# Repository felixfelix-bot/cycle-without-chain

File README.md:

# cycle-without-chain

An **independent-cadence, chainless electric drivetrain for a bicycle**: the rider
pedals a generator, a power-electronic bus moves the energy, and hub motors drive
the wheels. Cadence is decoupled from road speed, so the rider can pedal at a
comfortable speed and torque while the electronics do the job a gear train would
otherwise do.

> **STATUS: DESIGN PHASE. NOT SAFE TO ENERGIZE. NOT FABRICATED. NOT ROAD LEGAL.**
> A schematic and a body of analysis exist. There is no PCB, no assembly, no
> energised hardware and no measured prototype performance. Nothing here
> authorises building, powering or riding anything. The safety architecture below
> is an intent backed by calculations, not a qualified design.

## What is being built

**pedals → generator → controlled DC bus → hub motor(s) → wheels.** There is no
chain to the rear wheel.

- **Two motor/generator bridges** driven by DRV8353 smart gate drivers, six 2 mΩ
  low-side shunts, a 29-MOSFET population. Generator and motor are electrically
  independent, which is what makes cadence independent of road speed.
- **Rider effort is a generator load**, not a mechanical coupling. Pedal
  resistance is set electrically; arbitrary cadence and arbitrary power cannot
  both be enforced simultaneously, and the rider/generator balance has to be
  managed.
- **Mechanical friction brakes remain mandatory and are not replaced** by
  electrical braking. Regeneration is only commanded by actual rider brake
  intent — never by a map, a predicted hill or a control loop.
- **Fault shutdown is separate from normal braking**, and must work whether or not
  the microcontroller has booted.

## Storage: LTO pack plus supercapacitor buffer

Chemistry is fixed by the operator: **lithium titanate (LTO) for usable energy, a
supercapacitor bank for power.** The split follows the duty this vehicle actually
has — a short-duration buffer for starts, stops and brief deficits, with no
powered-range target.

- Preferred string to evaluate: **20s Toshiba SCiB 2.9 Ah cells** — 56.0 V max,
  48.0 V nominal, 36.0 V min, ≈139 Wh and ≈3.0 kg cells only.
- **56.0 V sits inside the existing 36–58.4 V bus envelope**, so the bus voltage
  survives the LTO decision. This is a window fit, not a compatibility proof:
  loaded terminal voltage under pulse current, tolerance stack-up, fuse and
  disconnect behaviour, and cold/full charge acceptance all remain open.
- The supercapacitor branch (candidate: Eaton XV3550 20s, ≈1.24 kg, ≈3.9 Wh usable)
  is **not additive by default**. It is justified only if measured braking energy
  demonstrably exceeds LTO charge acceptance, or if cold operation requires it.

Record: [storage decision](docs/design/storage-decision-lto.md).

## What the trade study found

Why this project needs a careful design phase rather than a fast build:

- A waxed derailleur chain is roughly **96%** efficient. A series electrical path
  is not, and every conversion stage compounds.
- A realistic purpose-built PM generator path — generator × rectifier × controller
  × motor ≈ 93% × 97% × 98% × 90% — lands near **80%**, roughly a **20-point
  loss**. An automotive claw-pole alternator at bicycle cadence is far worse
  (≈21–39%) because those machines are built for 1500+ rpm.
- Consequence: at equal wheel output the rider must produce roughly **20% more
  pedal power** than with a chain. That is the price of independent cadence and
  the single number to decide against.
- Cases where a series drivetrain genuinely earns its losses: long-wheelbase cargo
  bikes, velomobiles with many idlers, and layouts where crank speed must be
  decoupled from wheel speed. A simple bicycle with a chain does not need this.

The study, its assumptions and its known accounting errors:
[docs/analysis/chainless-drivetrain.md](docs/analysis/chainless-drivetrain.md). Its
model is retained **unchanged** for audit, including the errors.

**Published correction:** earlier notes claimed Mando Footloose and Schaeffler Free
Drive use automotive claw-pole alternators and deliver ~32% pedals-to-road. No
verified generator-efficiency map exists for either product. Do not reuse that
figure as a product specification. See
[the illustrated guide](docs/analysis/parallel-hybrid-guide.md) for source boundaries.

## Schematics

`hardware/powerboard-reva/` is a Python generator that emits a hierarchical
**KiCad 9** schematic, native netlist, PDF and SVG. Current state:

- **387 components, 220 nets, 1142 connected pins, 51 explicit NCs, 32 pages.**
  The pre-change baseline was re-measured from a fresh clone at `ae42054`
  (382 components, 218 nets, 1129 pins): [schematic figure verification](docs/design/schematic-figures-verified.md).
  The current figures include the DRIVE12 OVP comparator, its divider and the L501 change.
- **49 hardware tests** pass, normally and under `python3 -O`.
- Strict ERC: **0 errors, 0 warnings, exit 0** — the ten former undriven-supply
  findings are resolved by ten justified `PWR_FLAG`s (see
  `docs/design/erc-power-flags.md`); the verifier now requires ERC to be empty.
  Enumerated, gate-enforced and treated as open work, not silenced.
- Blocks present: dual DRV8353 bridges; protected-entry *intent* (fuse, shunt
  reverse clamp, 22 Ω resistor precharge, back-to-back TPSI3052-driven MOSFET
  pairs); fast overcurrent comparators; dual FSR brake frontends; rail partition
  (pack→CTRL3V3, bus→SINK12 always-on safety chain, delayed DRIVE12→MCU3V3) with
  an independent DRIVE12 output OVP comparator; and a pack-side control supply.
- **Inhibit resistors hold every switch off without firmware** — fitted 0 Ω ties,
  deliberately present, not to be removed.

**What does not exist:** no `.kicad_pcb`, no placement, no routing, no Gerbers, no
priced purchase BOM, no assembled board, no bench measurement of any kind.

## The definition of done

[Open gates register](docs/design/open-gates-register.md) states what is proven and
what is not: **109 gates**, each classified by the kind of evidence that closes it.

- **A — closable now** by calculation, part selection, topology change or
  simulation, without hardware.
- **B — needs a built board** (thermal, ripple, effective capacitance under DC
  bias, start-up sequencing, EMI, hot-plug, pulse/SOA, main-switch conduction).
- **C — needs an operator decision.**
- **D — resolved**, with the commit that closed it.

Per-bucket counts are deliberately **not** repeated here. They move whenever a gate
is closed, and a stale copy in the README is exactly the drift this register exists
to prevent. The register's own summary table is authoritative, and
`analysis/gates/register_check.py` fails if it disagrees with the rows above it.

**The design phase is complete when every A gate is closed and every B and C gate
is explicitly deferred to a named phase with a named owner.** It is not complete
when the board works, because the board has never existed. Finishing the register
claims no electrical safety, no road legality and no manufacturing readiness.

That document is kept honest mechanically: `analysis/gates/register_check.py` fails
if a row has no bucket, no citation or a duplicate ID, or if the bucket counts
disagree with the summary table. It verifies the register is complete and
countable — not that any engineering claim inside it is true.

### Decisions still needed from the operator

Each is a C gate with its consequence recorded in the register:

1. **Architecture** — the study recommends the parallel hybrid; the chainless
   series version is an explicit overrule. Recording it matters because it sets the
   ~20-point rider-power cost and removes pedalling home on a flat battery.
2. **Road class and jurisdiction** — sets lawful power, speed and control topology.
3. **Motor and generator** — pole count, Kv, winding. Bus voltage, shunts, trip
   points, regen ceiling and body-diode energy all follow from it.
4. **Pack and BMS** — exact cell, series count, current limits, source impedance.
5. **Mass and frame** — weighed bicycle mass, frame and fork, permitted mounting.
6. **Duty and route** — descent grades, duration and ambient, which set the braking
   sink rating.
7. **Test authority** — what energy may be tested, in what guarded setup, signed
   off by whom. Every B gate is blocked until this exists.
8. **Independent reviewer** — no review in this corpus can claim cross-family
   independence.

## Quality gates

The board tooling was rebuilt after auditing a previous project where a failed DRC
subprocess reported zero violations — a fail-open check that reads as a clean board.
Those lessons are executable here, not documented intent:

- `tools/gates/native_reports.py` — KiCad export/DRC/ERC runner. A nonzero exit, a
  missing or unparsable report, a stale report, or a zero-object scan is
  **FAILURE**, never success.
- `tools/gates/netlist_parity.py` — exact `(reference, pin, net)` set comparison.
  Counts are never compared, because a gate/source swap keeps the count identical.
- `tools/gates/release_manifest.py` — manufacturing artifact inventory rejecting
  placeholder, truncated or missing outputs, including a requested inner layer that
  produced no file.
- `tools/gates/run_all_gates.py` — one nonzero status if any gate fails; a crashed
  or unwired gate reports **NOT RUN**, never green.

**237 gate tests pass**, normally and under `python3 -O`, with negative controls
proving each gate can actually fail.

## Use cases under investigation

These are **hypotheses to test, not market validation**. The series concept trades
conversion losses, added mass and control complexity for cadence independent of
road speed, controllable pedal resistance and chassis freedom. This is research,
not a certified product.

- **Cargo and urban logistics:** a comfortable cadence through stops and changing
  road speeds. Payload and hill capability remain bounded by motor torque,
  available power, storage state and thermal limits — not guaranteed.
- **Adaptive cycling and rehabilitation research:** adjustable pedal resistance
  could support experiments with different rider abilities. Suitability requires
  individual assessment; no medical safety or treatment claims.
- **Low-maintenance, clean commuters:** removing the wheel-drive chain could reduce
  chain grime and servicing, but does not guarantee lower total maintenance. The
  crank-to-generator gearing remains moving machinery and needs a guard.
- **Recumbent, velomobile and alternative-chassis designers:** electrical routing
  could replace long wheel-drive chains and free up layout, subject to generator
  packaging, structural loads, mass and heat rejection.
- **Stationary exercise and pedal charging:** controlled resistance could convert
  rider effort into stored energy — not free energy. Requires a safe, stable stand
  and wheel-propulsion inhibit. At full storage, useful charging stops; continued
  pedalling under load needs a safe energy sink and cooling.

### Balance assistance — research option, not a feature

An actively gimballed flywheel might assist stopping, starting and mounting for
riders with balance limitations. This is an accessibility hypothesis, not
demonstrated safety or fall prevention, and it is compared against mechanically
supported cycles including tricycles.

Energy scales with rotor speed squared; angular momentum only linearly. Discharging
the rotor reduces balancing authority. Two gimbal axes do not eliminate torque
coupling, travel limits, singularities or power-failure risk. The suggested 8–12 kg
mass and 30% range penalty are unverified examples, not specifications. Never claim
recovery from ice, potholes, collisions or arbitrary disturbances, and never claim
the rider cannot tip over. High-speed rotor safety needs specialist mechanical
engineering, not electrical PCB checks.

[Quantified feasibility study](docs/design/gyro-balance-feasibility.md) — calculations
and a source-backed shortlist, not a purchase BOM. No gyro hardware is selected, and
mechanical brakes and support are not replaced.

## Repository map

- `hardware/powerboard-reva/` — schematic generator, tests, committed netlist/PDF/SVG
  exports. The generator is the source of truth, not the exports.
- `docs/design/` — per-block milestone and review documents, the
  [open gates register](docs/design/open-gates-register.md), the
  [LTO storage decision](docs/design/storage-decision-lto.md), and the gyro study.
- `docs/analysis/` — drivetrain trade study, historical model, diagrams.
- `analysis/` — executable models with tests: precharge, braking, storage, gyro,
  navigation, FSR, register consistency.
- `tools/gates/` — the fail-closed release gates.
- `docs/evaluation/`, `docs/research/`, `docs/PLAN-parallel-hybrid.md` — **historical**
  concept and sourcing research from the parallel-hybrid baseline. Not validated
  purchasing evidence, and not the current implementation plan.

## Reproduce

```sh
# drivetrain trade study (stdlib only)
python3 docs/analysis/chainless_drivetrain_model.py

# schematic, netlist, PDF and SVG
cd hardware/powerboard-reva && python3 generate_schematic.py

# hardware test suite, both modes
cd hardware/powerboard-reva && python3 -m unittest discover -s tests
cd hardware/powerboard-reva && python3 -O -m unittest discover -s tests

# fail-closed release gates — pytest only, see the note below
python3 -m pytest tests/gates -q

# open-gates register consistency
python3 analysis/gates/register_check.py docs/design/open-gates-register.md
```

### `tests/gates` has no unittest route

Every test under `tests/gates` is a **bare module-level function**, and the whole
directory contains **zero `unittest.TestCase` classes**. `python3 -m unittest
discover -s tests/gates` exits **0** reporting `Ran 0 tests … OK`: it grades
nothing. Adding `tests/gates/__init__.py` does not change this — the collection
unit unittest looks for is a `TestCase` subclass, which these files do not have.

That is why the gate count is quoted from `python3 -m pytest tests/gates -q`
(**237**) and never from a unittest command. If you add a gate test, use pytest
and keep it a function; converting the directory to `TestCase` classes would be a
deliberate change to how the suite is collected, not a cleanup.

The hardware suite under `hardware/powerboard-reva/tests` is different: it is
`unittest` throughout, so the `unittest discover` command above is correct there
and reports **49** tests.

Passing tests prove the models and the generated connectivity behave as specified.
They do not prove the circuit is electrically safe, fabricable or rideable.

## Remotes

The repository is published in two places, and both are live:

- **GitHub** — `origin`, <https://github.com/felixfelix-bot/cycle-without-chain>
- **nostr (NIP-34)** — `ngit`, via `relay.ngit.dev`

```
git clone nostr://npub1tc6a0gdsu5l5gplyxflgwy9aq29jyelj9rv65syyukx3setl0usq9npkea/relay.ngit.dev/cycle-without-chain
```

Web view: <https://gitworkshop.dev/npub1tc6a0gdsu5l5gplyxflgwy9aq29jyelj9rv65syyukx3setl0usq9npkea/relay.ngit.dev/cycle-without-chain>

Push to both with `git push origin master && git push ngit master`. The nostr
identity (`npub1tc6a0…`) is dedicated to this repository; its secret is held in
ngit's local file store, not in this tree.

*Earlier history: the repository previously carried a ngit remote for
`npub1nng5…` that never had a published announcement, so it was a dangling
coordinate rather than a working mirror. It was replaced by the current identity
on 2026-11-11; the old coordinate is dead and should not be used.*

## License

Model and analysis code MIT; documentation separately licensed. See `LICENSE`.

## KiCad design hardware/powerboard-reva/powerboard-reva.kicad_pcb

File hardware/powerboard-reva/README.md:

# Powerboard Rev A — populated, partial schematic milestone

**NOT SAFE TO ENERGIZE. NOT FABRICATION-READY. No PCB, routing, procurement or riding authorization.**

Open `powerboard-reva.kicad_pro` or root `powerboard-reva.kicad_sch` in KiCad 9. The root references twenty-six real child sheets. Nets join electrically through explicitly named global labels; GEN_ and HUB_ prefixes separate bridge/control signals. This is not a block-diagram-only drawing or connector substitution for ICs.

## Selected FSR circuit milestone (current; supersedes historical counts below)

Two actual OPA333AIDBVR + TMUX1511PWR channels now replace the rider Hall inputs.
See [FSR implementation](docs/fsr-implementation.md). The binary switch topology remains;
its authority is a **firmware contract, not a hardware positive-torque guard**.
27 pages, 314 components, 181 connected nets, 956 connected endpoints, 51 explicit NCs.
Strict ERC returns **5**, with **5 unresolved errors / 0 warnings**; no suppression.
Candidate TVS/clamps are not battery-short protection. Low-voltage frontend bench use
only after independent review; this does not authorize energizing the powerboard.

## Current MCU milestone (historical; superseded by FSR counts above)

See [MCU integration review](../../docs/design/mcu-integration-review.md) for reproduced checks, pending cross-family approval and prioritized next circuit blockers. [MCU milestone](../../docs/design/mcu-milestone.md): real STM32G474VET6 circuit, 15 pages, 199 components, 642 connected endpoints and 45 explicit NC pins. Native ERC: four unresolved errors, zero warnings. Firmware, fast overcurrent trip, protected entry, storage acceptance and sequencing remain blockers. Historical sections below are not current status.

## Current protection integration — UNSAFE DRAFT

The sections below record the **earlier six-page milestone**, not current counts.
Current integration has 10 pages, 130 components, 104 nets and 452 endpoints;
VM now uses bus-fed AUX12V. Four added protection sheets remain unqualified.
See [independent integration review](../../docs/design/protection-integration-review.md)
for current evidence and prioritized blockers. ERC still has three errors
(U1.24 VREF, U1.25 AGND, U3.1 DC_LINK). No release approval.

## Implemented (historical six-page milestone)

- Two **DRV8353SRTAT** SPI drivers, 40 signal pins plus exposed pad, from TI SLVSDY6A pp6–7.
- Twelve **CSD19532Q5B** MOSFETs using embedded, inheritance-resolved stock KiCad symbols; three half-bridges per machine.
- Twelve provisional 4R7 gate resistors and twelve 100k gate-source pull-downs.
- Six 2mOhm low-side shunts, each wired to the corresponding SPx input and low-side sources; SNx to PGND. Kelvin layout is mandatory and not yet implemented.
- Driver charge-pump, regulator and supply capacitors; ENABLE pull-downs; SPI SDO/nSCS and fault pull-ups.
- Six provisional local 1uF/100V bus ceramics and one provisional 100uF/100V bulk capacitor.
- Eleven explicitly external connectors for machine phases, protected DC input, regulated supplies, independent enable chain, MCU PWM/SPI/ADC.

VM deliberately uses externally regulated 12V; VDRAIN senses the shared bus. VREF is 3.3V, **not** 1.65V: CSA midpoint comes from internal VREF/2. Gain20 and driver protection configuration require software plus hardware review; no configuration is implied by the drawing.

## Executed verification (KiCad CLI 9.0.9)

Run `python3 export_artifacts.py` from this directory. Python standard library and installed KiCad symbol libraries are sufficient; no SKiDL runtime required. Direct native schematic generation was used to deliver loadable drawings, not only a netlist.

- Six loadable hierarchical pages: root, GEN driver, GEN bridge, HUB driver, HUB bridge, external boundaries.
- **84 components, 80 exported nets, 308 pin assignments** checked against the actual KiCad-exported netlist by `verify_exports.py`.
- Actual six-page PDF: `exports/powerboard-reva.pdf`.
- Six nonempty SVG pages: `exports/svg/`.
- Actual netlist: `exports/powerboard-reva.net`.
- Actual ERC: `exports/erc.rpt` — **3 errors, 0 warnings**, all `power_pin_not_driven` for external AUX12V_EXT, LOGIC3V3_EXT and PGND supply boundary. No PWR_FLAG or waiver masks these unresolved boundaries. CLI exiting zero is not a clean ERC verdict.
- Machine-readable counts: `exports/verification.json`; component list `review-bom.csv`; exact mapping `pin-net-map.csv`.
- PDF bridge page visually inspected: real populated circuit visible, no clipping/major block overlaps, but dense local MOSFET labels need drawing cleanup before formal review.

## Explicit release blockers

This intentionally **does not implement** the complete eight-sheet concept. Missing: fused/reverse-protected/precharged power entry, DC contactor and discharge, independent OV comparator/chopper/resistor/thermal cutout, current comparator and latched fault chain, brake interlock, watchdog, UVLO, auxiliary buck/3V3 rails, bus-current INA240 circuit, MCU/SWD/timer/ADC mux, Hall/encoder/temperature interfaces and storage/BMS acceptance logic. No optional storage DC/DC exists.

External connectors are interface contracts for those unfinished circuits, **not evidence that they exist**. ENABLE pull-downs and integrated driver OCP are not a complete safety system. PM machines can charge the bus through body diodes even with all gates off. No validated thermal/ripple/transient model, source interrupt ratings, EMC review or full-energy test exists.

DRV footprint is deliberately blank pending exact RTA land-pattern/thermal-pad verification (pad41 is a schematic convention). Many passive and connector footprints are unselected. Stock MOSFET and shunt footprints are candidate mappings, not fabrication qualification. Gate resistances, capacitor values and connector pin orders are provisional, not an orderable BOM. No unselected safety part is disguised as a DNP implementation.

Independent review must validate electrical and physical pin maps against primary package drawings, supply sequencing/back-powering, CSA calibration/PWM sampling, gate drive/current/OCP settings and all safety failure modes. Then close ERC and protection design before any layout release. Reviewers should retain the honest partial status even though all connectivity assertions pass.

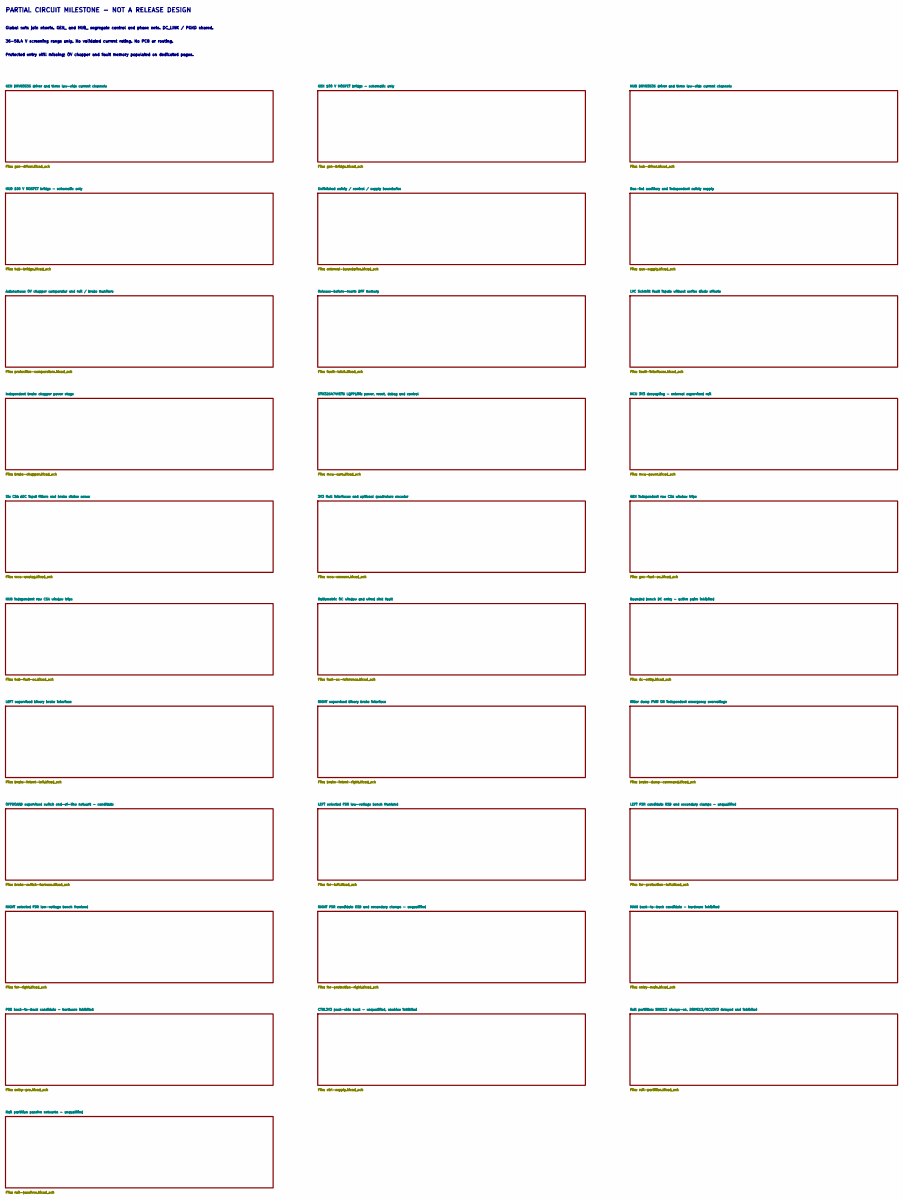
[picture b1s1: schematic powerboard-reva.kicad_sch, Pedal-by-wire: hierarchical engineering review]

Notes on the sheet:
PARTIAL CIRCUIT MILESTONE - NOT A RELEASE DESIGN
Global nets join sheets. GEN_ and HUB_ segregate control and phase nets. DC_LINK / PGND shared.
36-58.4 V screening range only. No validated current rating. No PCB or routing.
Protected entry still missing; OV chopper and fault memory populated on dedicated pages.

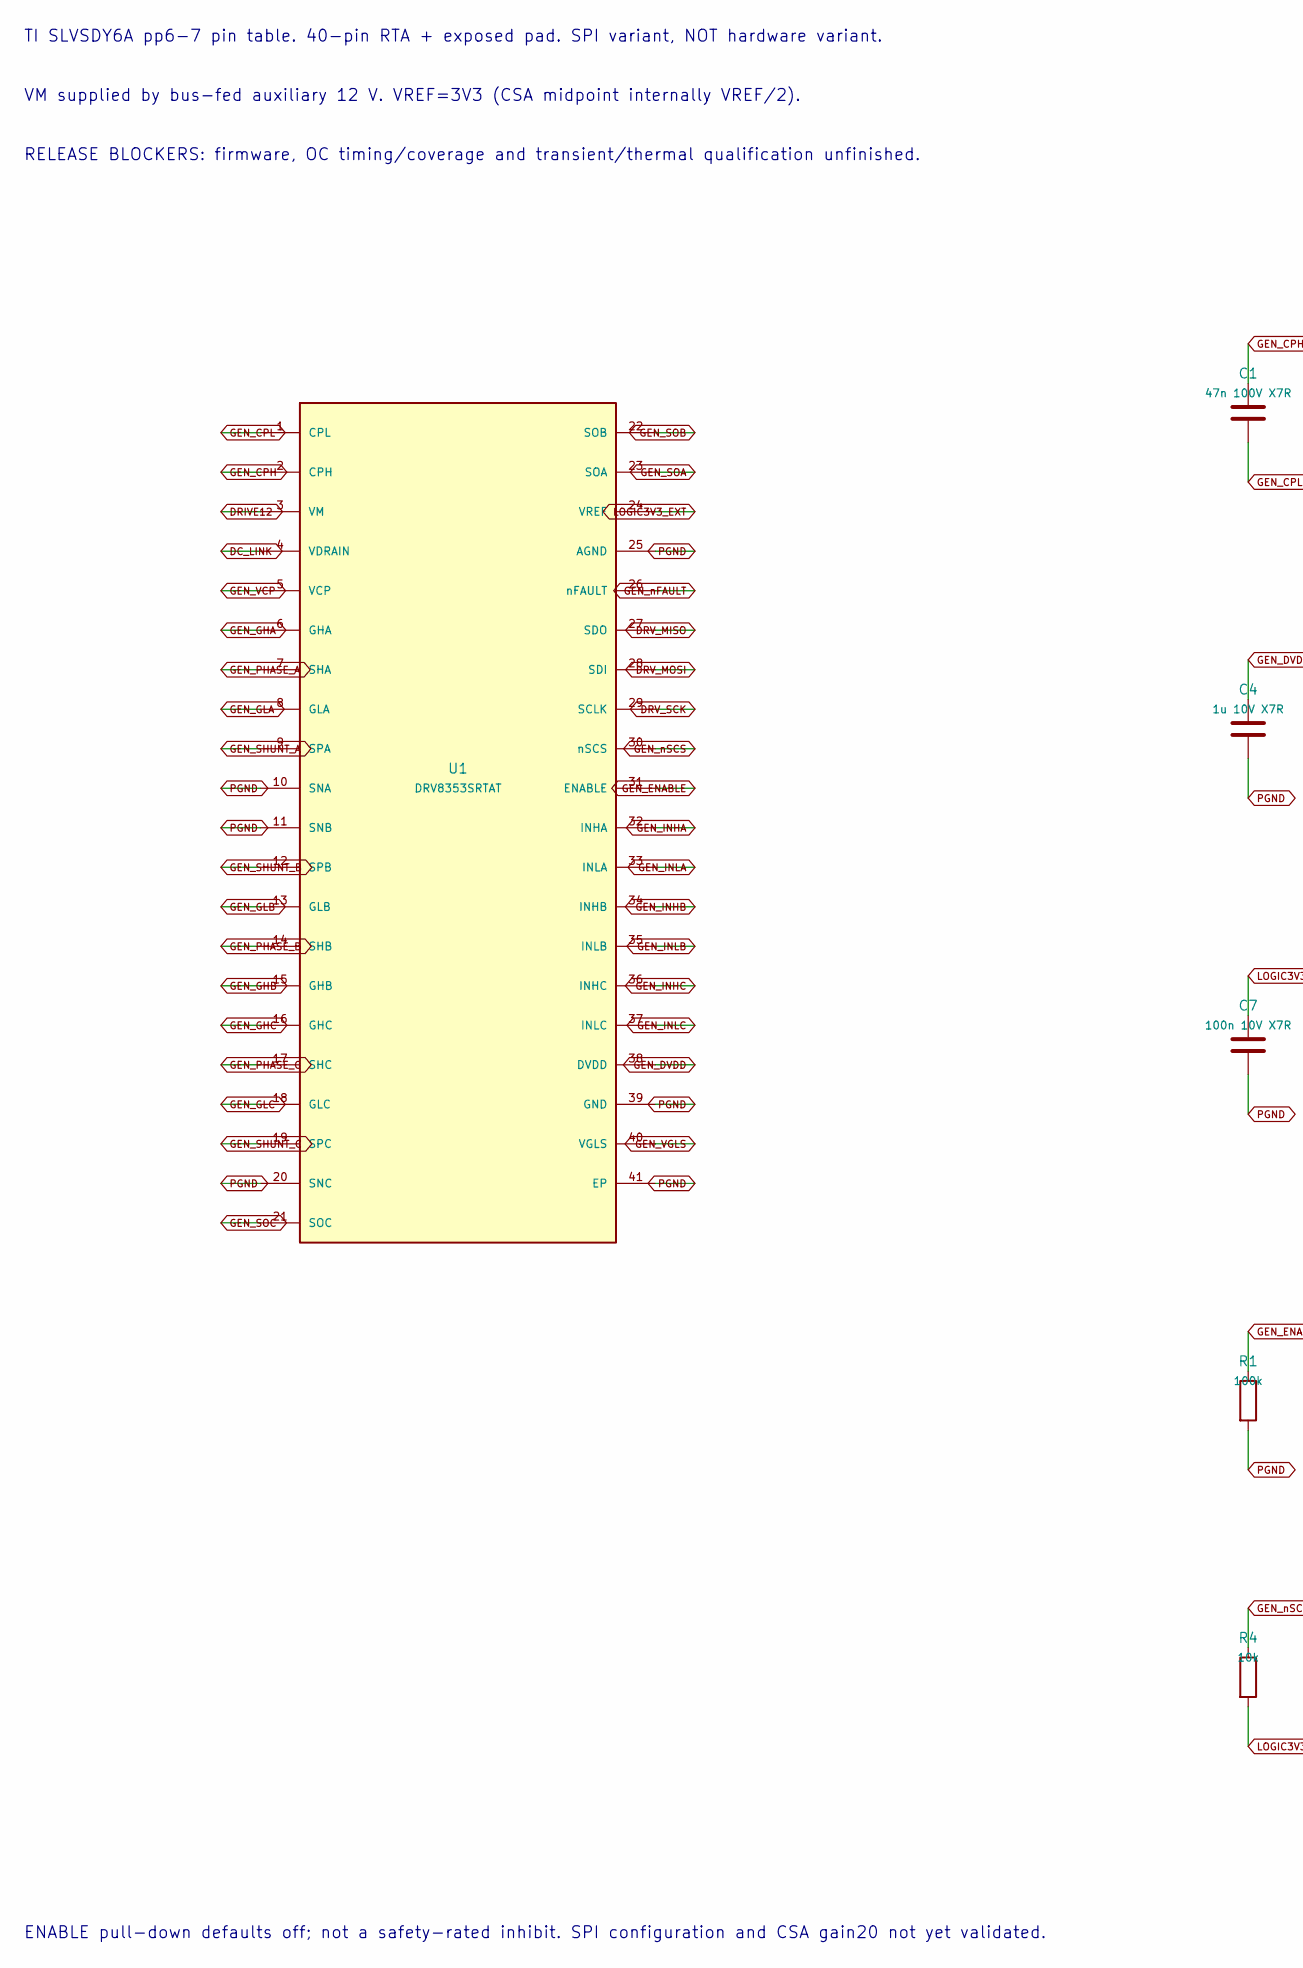
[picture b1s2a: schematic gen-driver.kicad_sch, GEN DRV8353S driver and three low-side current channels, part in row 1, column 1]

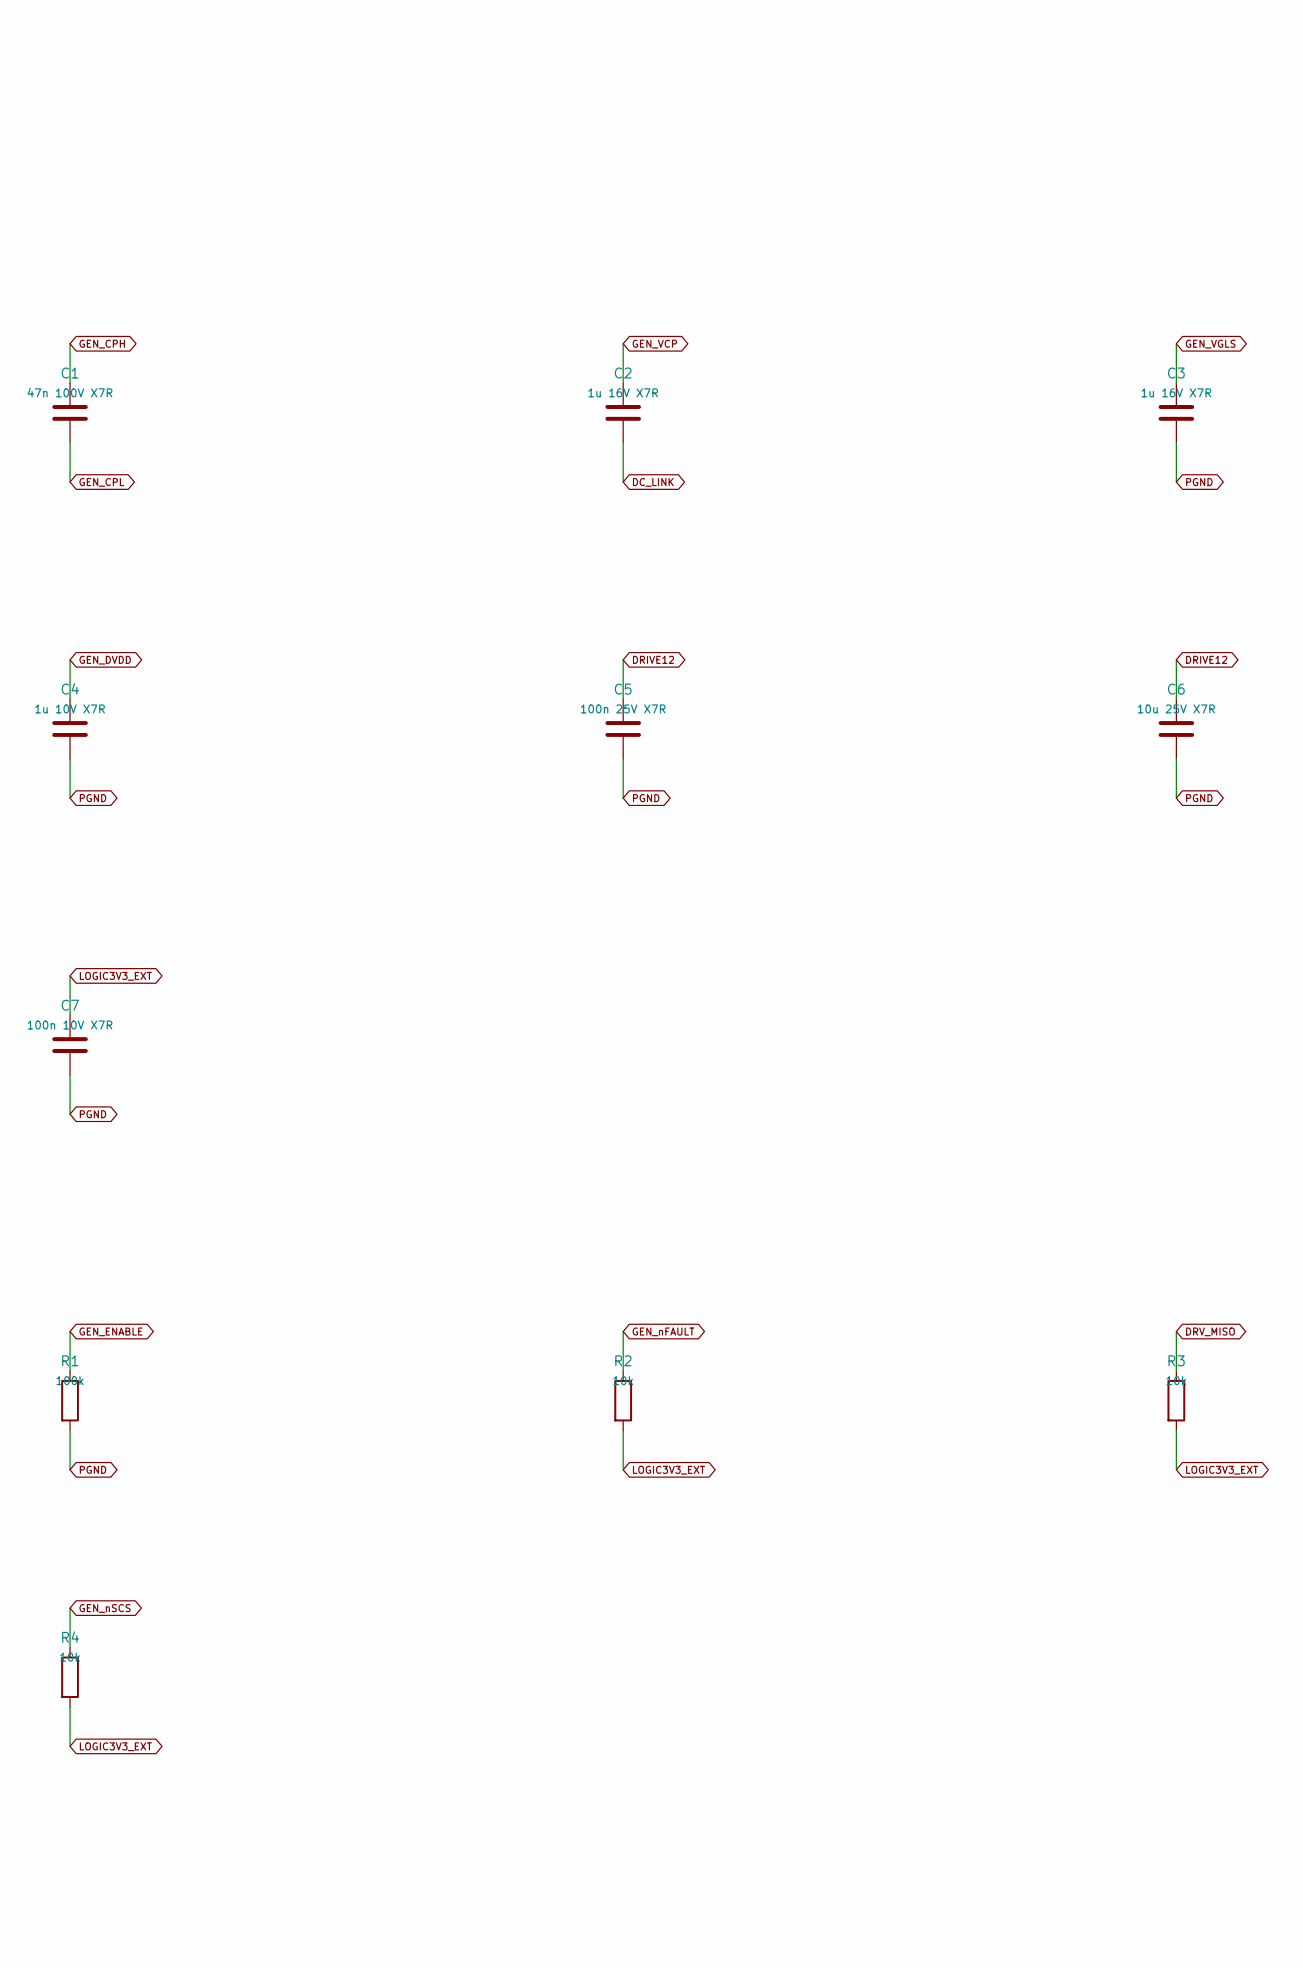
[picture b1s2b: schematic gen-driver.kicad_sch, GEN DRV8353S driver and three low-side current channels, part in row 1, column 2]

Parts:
C1: 47n 100V X7R; C_0805_2012Metric
C2, C3: 1u 16V X7R; C_0805_2012Metric
C4: 1u 10V X7R; C_0603_1608Metric
C5: 100n 25V X7R; C_0805_2012Metric
C6: 10u 25V X7R; C_0805_2012Metric
C7: 100n 10V X7R; C_0603_1608Metric
R1: 100k; R_0805_2012Metric
R2, R3, R4: 10k; R_0805_2012Metric
U1: DRV8353SRTAT; QFN-40-1EP_6x6mm_P0.5mm_EP4.6x4.6mm

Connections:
DC_LINK: C2.2, U1.4 (VDRAIN); also elsewhere on the board
DRIVE12: C5.1, C6.1, U1.3 (VM); also elsewhere on the board
DRV_MISO: R3.1, U1.27 (SDO); also elsewhere on the board
DRV_MOSI: U1.28 (SDI); also elsewhere on the board
DRV_SCK: U1.29 (SCLK); also elsewhere on the board
GEN_CPH: C1.1, U1.2 (CPH)
GEN_CPL: C1.2, U1.1 (CPL)
GEN_DVDD: C4.1, U1.38 (DVDD)
GEN_ENABLE: R1.1, U1.31 (ENABLE); also elsewhere on the board
GEN_GHA: U1.6 (GHA); also elsewhere on the board
GEN_GHB: U1.15 (GHB); also elsewhere on the board
GEN_GHC: U1.16 (GHC); also elsewhere on the board
GEN_GLA: U1.8 (GLA); also elsewhere on the board
GEN_GLB: U1.13 (GLB); also elsewhere on the board
GEN_GLC: U1.18 (GLC); also elsewhere on the board
GEN_INHA: U1.32 (INHA); also elsewhere on the board
GEN_INHB: U1.34 (INHB); also elsewhere on the board
GEN_INHC: U1.36 (INHC); also elsewhere on the board
GEN_INLA: U1.33 (INLA); also elsewhere on the board
GEN_INLB: U1.35 (INLB); also elsewhere on the board
GEN_INLC: U1.37 (INLC); also elsewhere on the board
GEN_PHASE_A: U1.7 (SHA); also elsewhere on the board
GEN_PHASE_B: U1.14 (SHB); also elsewhere on the board
GEN_PHASE_C: U1.17 (SHC); also elsewhere on the board
GEN_SHUNT_A: U1.9 (SPA); also elsewhere on the board
GEN_SHUNT_B: U1.12 (SPB); also elsewhere on the board
GEN_SHUNT_C: U1.19 (SPC); also elsewhere on the board
GEN_SOA: U1.23 (SOA); also elsewhere on the board
GEN_SOB: U1.22 (SOB); also elsewhere on the board
GEN_SOC: U1.21 (SOC); also elsewhere on the board
GEN_VCP: C2.1, U1.5 (VCP)
GEN_VGLS: C3.1, U1.40 (VGLS)
GEN_nFAULT: R2.1, U1.26 (nFAULT); also elsewhere on the board
GEN_nSCS: R4.1, U1.30 (nSCS); also elsewhere on the board
LOGIC3V3_EXT: C7.1, R2.2, R3.2, R4.2, U1.24 (VREF); also elsewhere on the board
PGND: C3.2, C4.2, C5.2, C6.2, C7.2, R1.2, U1.10 (SNA), U1.11 (SNB), U1.20 (SNC), U1.25 (AGND), U1.39 (GND), U1.41 (EP); also elsewhere on the board

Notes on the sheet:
TI SLVSDY6A pp6-7 pin table. 40-pin RTA + exposed pad. SPI variant, NOT hardware variant.
VM supplied by bus-fed auxiliary 12 V. VREF=3V3 (CSA midpoint internally VREF/2).
RELEASE BLOCKERS: firmware, OC timing/coverage and transient/thermal qualification unfinished.
ENABLE pull-down defaults off; not a safety-rated inhibit. SPI configuration and CSA gain20 not yet validated.

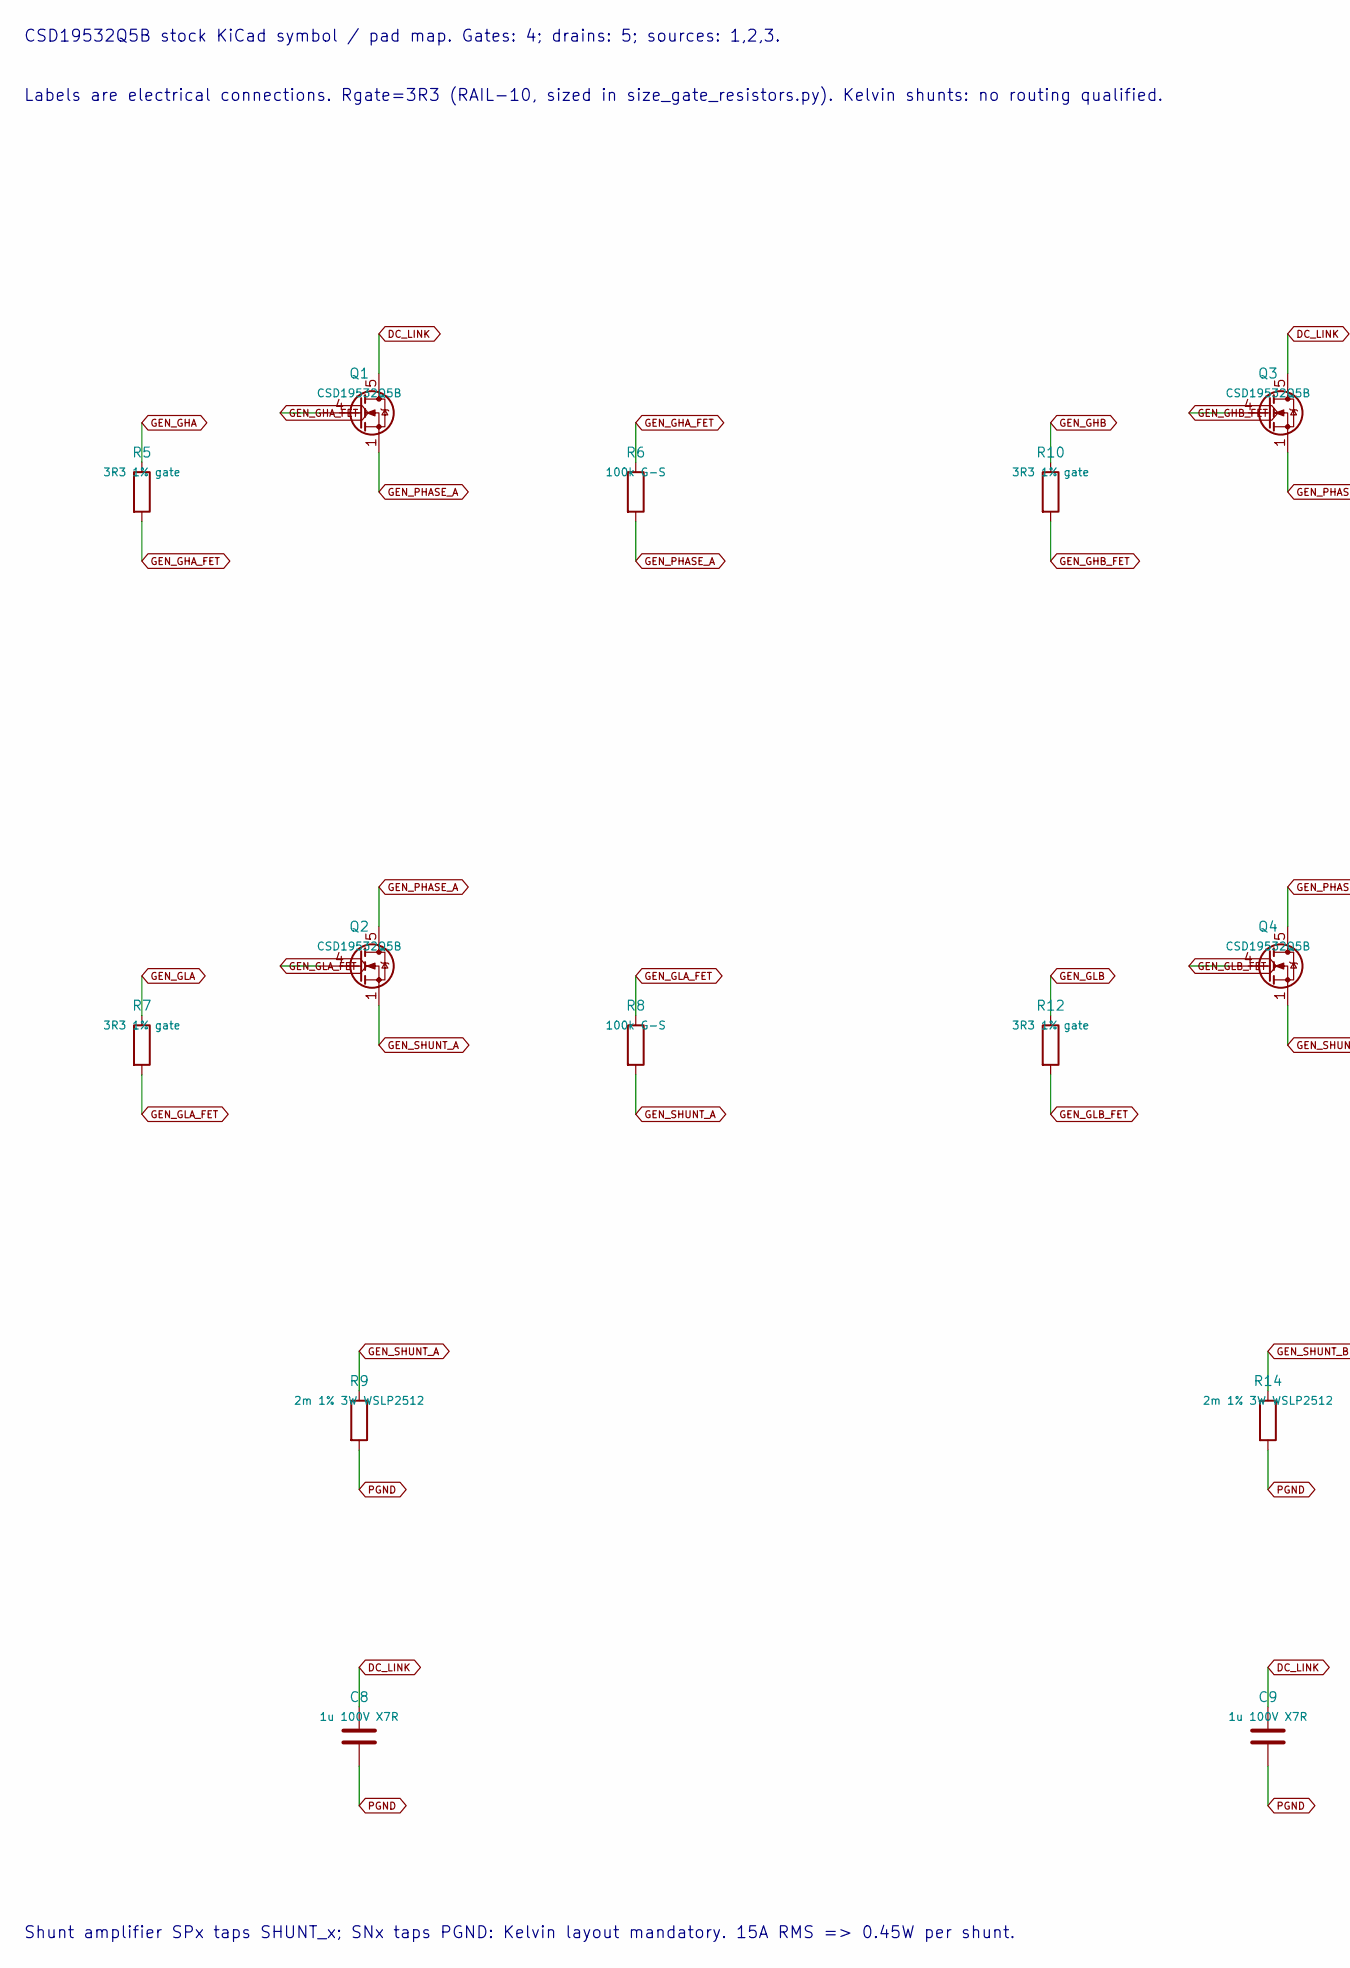
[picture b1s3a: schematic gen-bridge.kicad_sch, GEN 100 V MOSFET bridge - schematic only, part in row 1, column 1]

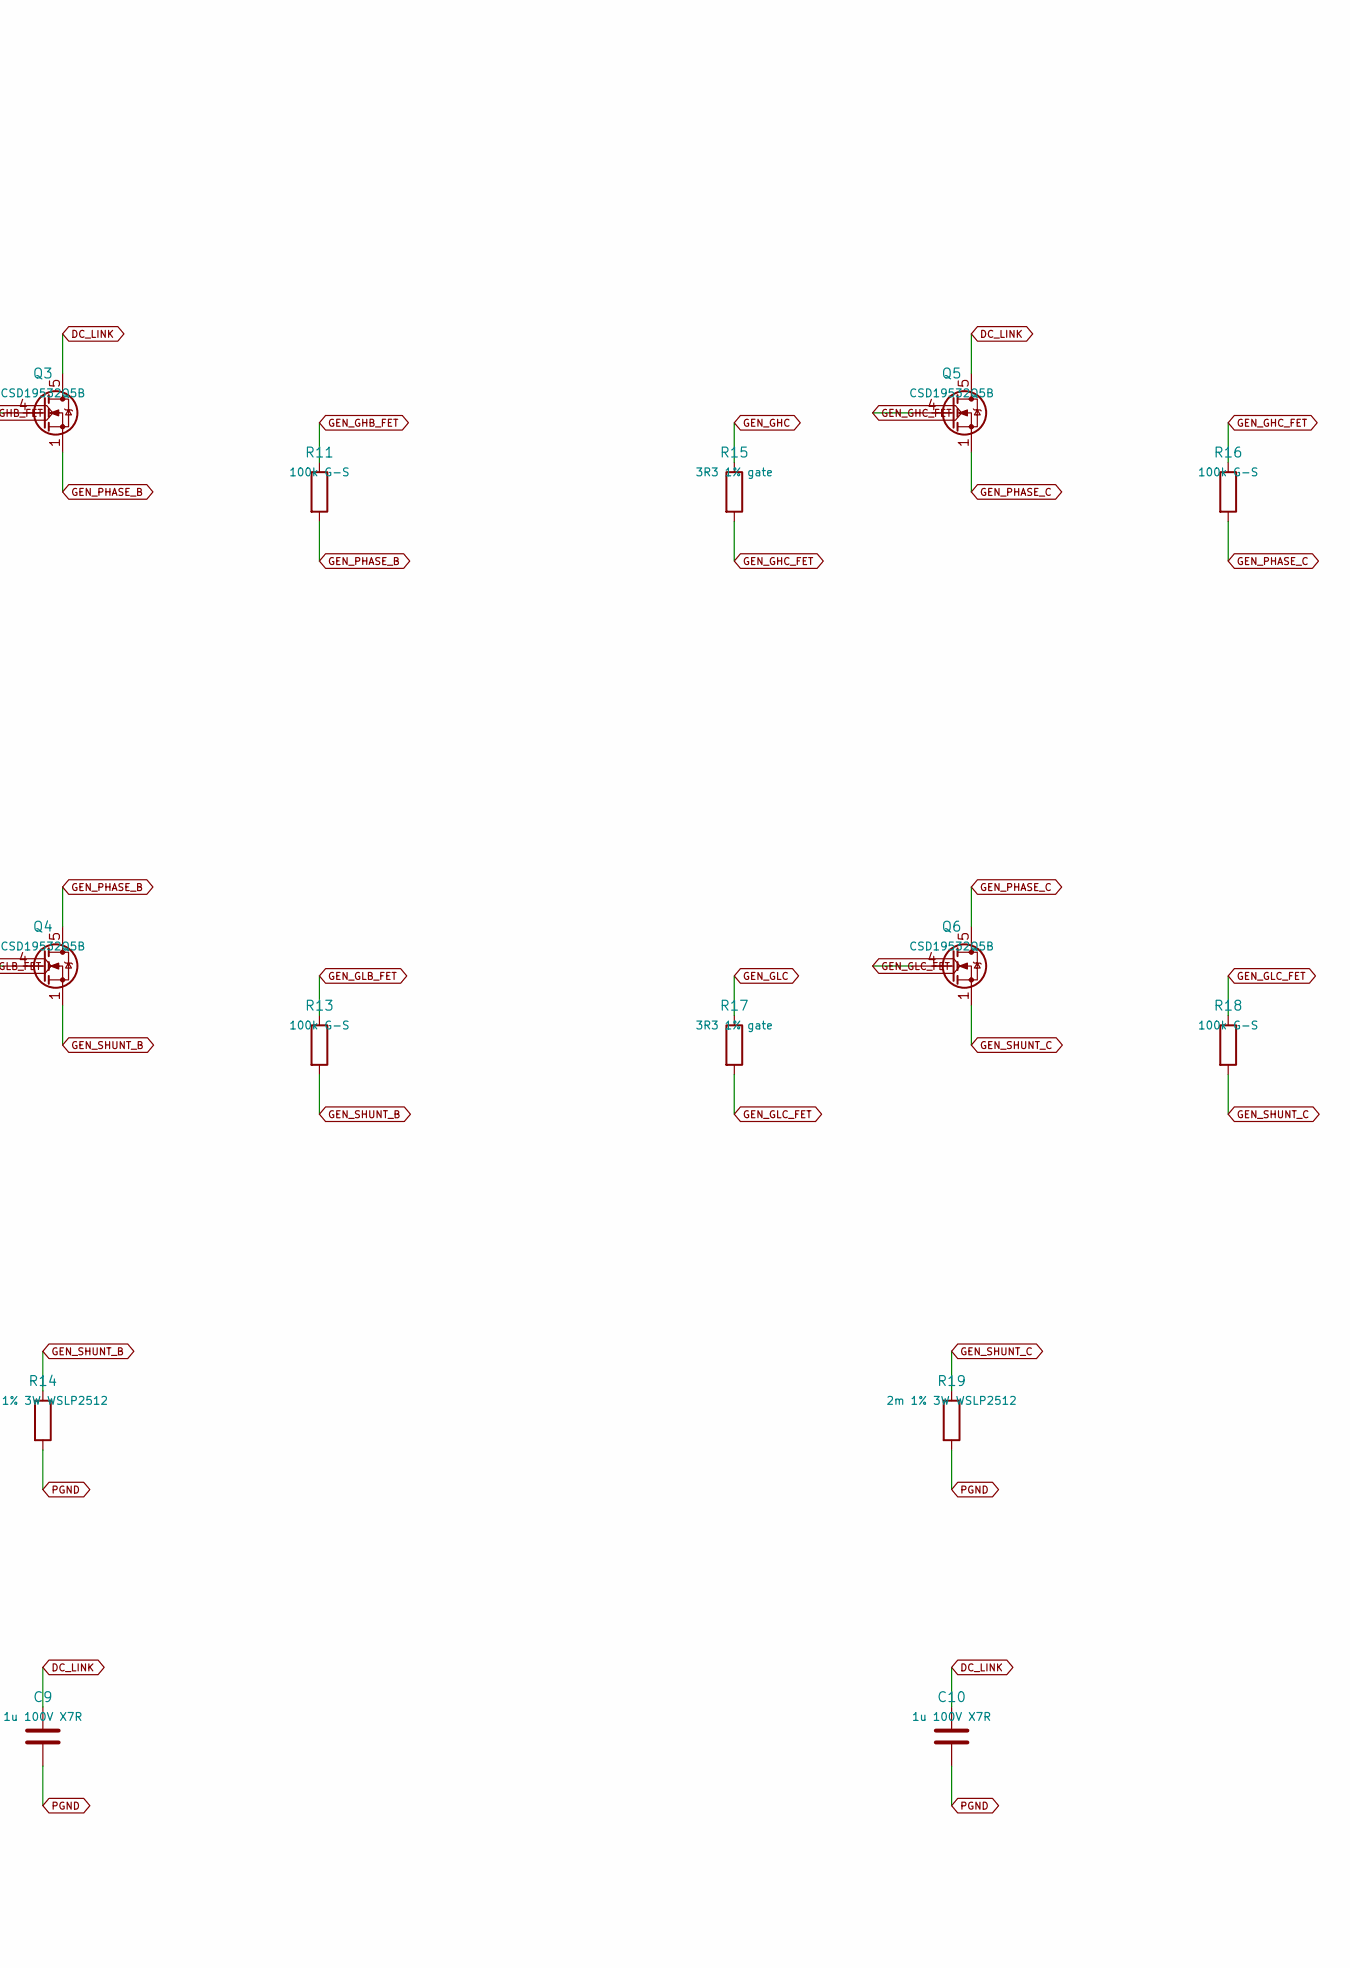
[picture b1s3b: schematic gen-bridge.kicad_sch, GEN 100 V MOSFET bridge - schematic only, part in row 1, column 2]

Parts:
C8, C9, C10: 1u 100V X7R; C_0805_2012Metric
Q1, Q2, Q3, Q4, Q5, Q6: CSD19532Q5B; TDSON-8-1
R5, R7, R10, R12, R15, R17: 3R3 1% gate; R_0805_2012Metric
R6, R8, R11, R13, R16, R18: 100k G-S; R_0805_2012Metric
R9, R14, R19: 2m 1% 3W WSLP2512; R_2512_6332Metric

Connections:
DC_LINK: C8.1, C9.1, C10.1, Q1.5 (D), Q3.5 (D), Q5.5 (D); also elsewhere on the board
GEN_GHA: R5.1; also elsewhere on the board
GEN_GHA_FET: Q1.4 (G), R5.2, R6.1
GEN_GHB: R10.1; also elsewhere on the board
GEN_GHB_FET: Q3.4 (G), R10.2, R11.1
GEN_GHC: R15.1; also elsewhere on the board
GEN_GHC_FET: Q5.4 (G), R15.2, R16.1
GEN_GLA: R7.1; also elsewhere on the board
GEN_GLA_FET: Q2.4 (G), R7.2, R8.1
GEN_GLB: R12.1; also elsewhere on the board
GEN_GLB_FET: Q4.4 (G), R12.2, R13.1
GEN_GLC: R17.1; also elsewhere on the board
GEN_GLC_FET: Q6.4 (G), R17.2, R18.1
GEN_PHASE_A: Q1.1 (S), Q1.2 (S), Q1.3 (S), Q2.5 (D), R6.2; also elsewhere on the board
GEN_PHASE_B: Q3.1 (S), Q3.2 (S), Q3.3 (S), Q4.5 (D), R11.2; also elsewhere on the board
GEN_PHASE_C: Q5.1 (S), Q5.2 (S), Q5.3 (S), Q6.5 (D), R16.2; also elsewhere on the board
GEN_SHUNT_A: Q2.1 (S), Q2.2 (S), Q2.3 (S), R8.2, R9.1; also elsewhere on the board
GEN_SHUNT_B: Q4.1 (S), Q4.2 (S), Q4.3 (S), R13.2, R14.1; also elsewhere on the board
GEN_SHUNT_C: Q6.1 (S), Q6.2 (S), Q6.3 (S), R18.2, R19.1; also elsewhere on the board
PGND: C8.2, C9.2, C10.2, R9.2, R14.2, R19.2; also elsewhere on the board

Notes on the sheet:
CSD19532Q5B stock KiCad symbol / pad map. Gates: 4; drains: 5; sources: 1,2,3.
Labels are electrical connections. Rgate=3R3 (RAIL-10, sized in size_gate_resistors.py). Kelvin shunts: no routing qualified.
Shunt amplifier SPx taps SHUNT_x; SNx taps PGND: Kelvin layout mandatory. 15A RMS => 0.45W per shunt.
